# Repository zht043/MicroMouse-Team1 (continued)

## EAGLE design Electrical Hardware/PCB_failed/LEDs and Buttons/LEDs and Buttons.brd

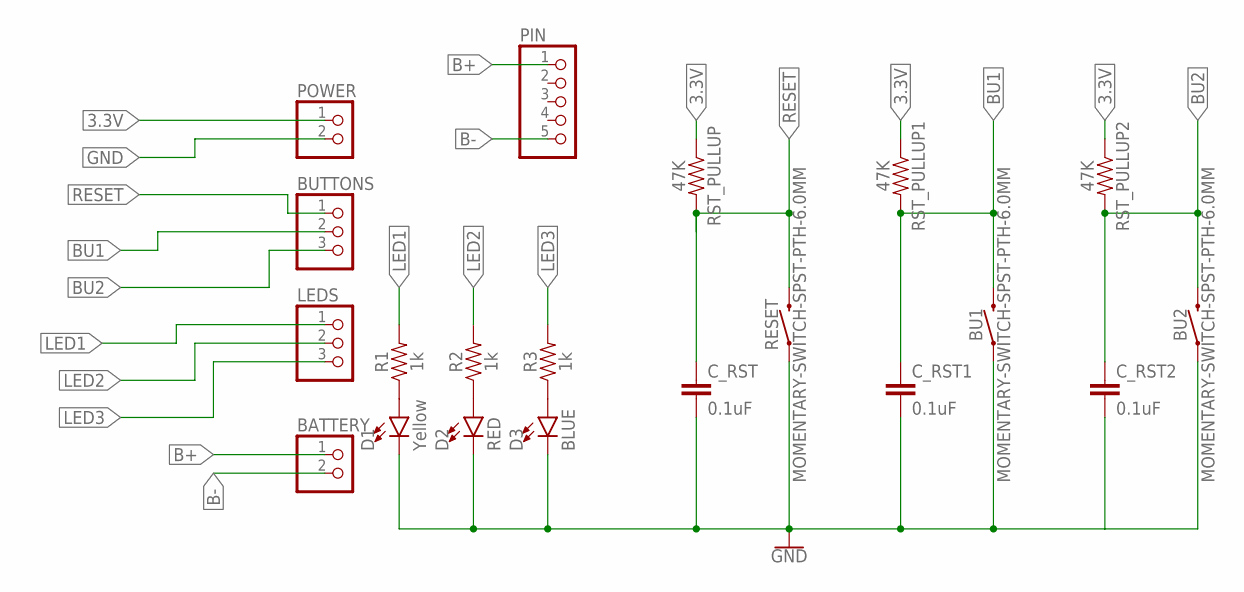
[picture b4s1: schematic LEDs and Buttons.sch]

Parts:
BATTERY: PINHD-1X2; 1X02
BU1, BU2: MOMENTARY-SWITCH-SPST-PTH-6.0MM; TACTILE_SWITCH_PTH_6.0MM
BUTTONS: PINHD-1X3; 1X03
C_RST, C_RST1, C_RST2: 0.1uF; 0805
D1: Yellow; LED-1206
D2: RED; LED-1206
D3: BLUE; LED-1206
LEDS: PINHD-1X3; 1X03
PIN: PINHD-1X55X2MM; 1_05X2MM
POWER: PINHD-1X2; 1X02
R1, R2, R3: 1k; 0805
RESET: MOMENTARY-SWITCH-SPST-PTH-6.0MM; TACTILE_SWITCH_PTH_6.0MM
RST_PULLUP, RST_PULLUP1, RST_PULLUP2: 47K; 0805

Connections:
3.3V: POWER.1, RST_PULLUP.1, RST_PULLUP1.1, RST_PULLUP2.1
B+: BATTERY.1, PIN.1
B-: BATTERY.2, PIN.5
BU1: BU1.3 (2), BUTTONS.2, C_RST1.1, RST_PULLUP1.2
BU2: BU2.3 (2), BUTTONS.3, C_RST2.1, RST_PULLUP2.2
GND: BU1.1, BU2.1, C_RST.2, C_RST1.2, C_RST2.2, D1.C, D2.C, D3.C, POWER.2, RESET.1
LED1: LEDS.1, R1.2
LED2: LEDS.2, R2.2
LED3: LEDS.3, R3.2
unnamed: D1.A, R1.1
unnamed: D2.A, R2.1
unnamed: D3.A, R3.1
RESET: BUTTONS.1, C_RST.1, RESET.3 (2), RST_PULLUP.2

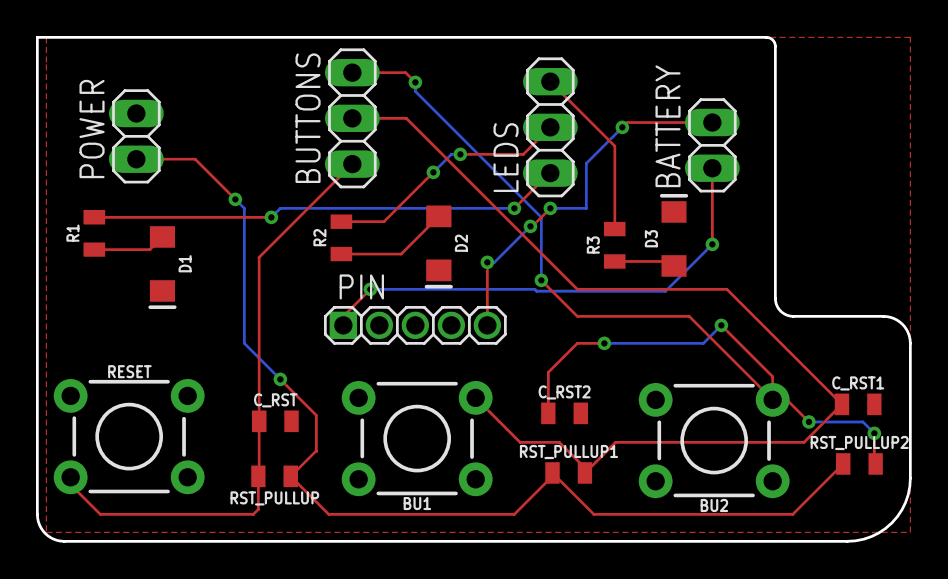
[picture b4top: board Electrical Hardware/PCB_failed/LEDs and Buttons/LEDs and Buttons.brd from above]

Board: 2 copper layers, 48.5 x 28.0 mm, 20 parts (0 on the bottom side), 13 nets.

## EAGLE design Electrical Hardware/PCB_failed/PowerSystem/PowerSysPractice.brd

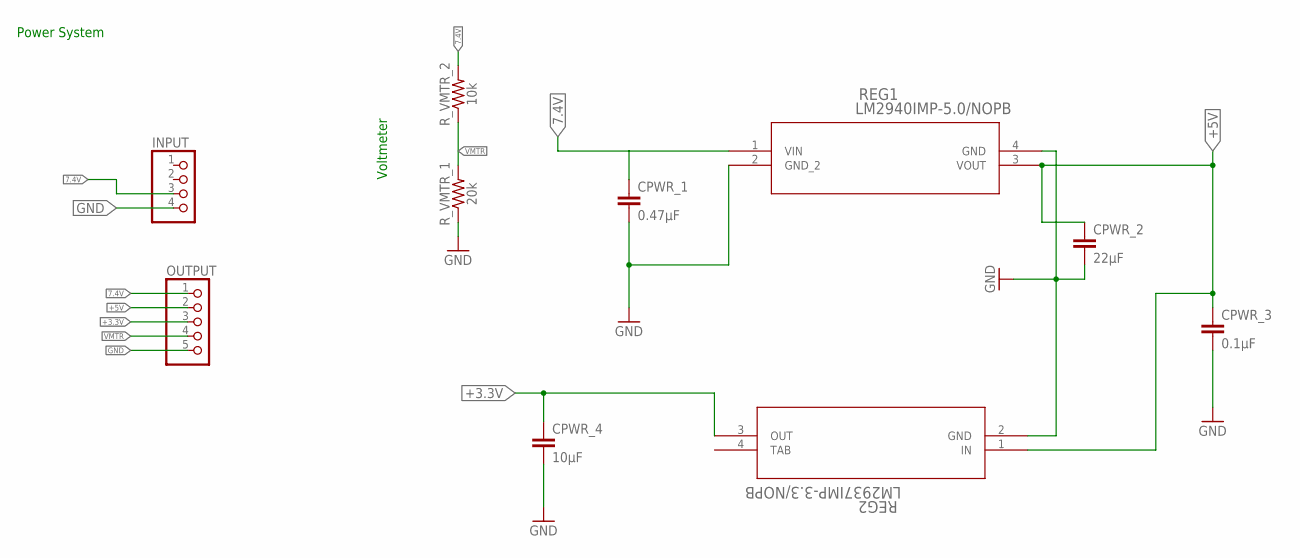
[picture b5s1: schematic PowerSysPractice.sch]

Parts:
CPWR_1: 0.47µF; 0805
CPWR_2: 22µF; 0805
CPWR_3: 0.1µF; 0805
CPWR_4: 10µF; 0805
INPUT: PINHD-1X4; 1X04
OUTPUT: PINHD-1X5; 1X05
REG1: LM2940IMP-5.0/NOPB; MP04A
REG2: LM2937IMP-3.3/NOPB; MP04A
R_VMTR_1: 20k; 0805
R_VMTR_2: 10k; 0805

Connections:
7.4V: CPWR_1.1, INPUT.3, OUTPUT.1, REG1.1 (VIN), R_VMTR_2.2
+3.3V: CPWR_4.1, OUTPUT.3, REG2.3 (OUT)
+5V: CPWR_2.1, CPWR_3.1, OUTPUT.2, REG1.3 (VOUT), REG2.1 (IN)
GND: CPWR_1.2, CPWR_2.2, CPWR_3.2, CPWR_4.2, INPUT.4, OUTPUT.5, REG1.2 (GND_2), REG1.4 (GND), REG2.2 (GND), R_VMTR_1.1
TAB: REG2.4 (TAB)
VMTR: OUTPUT.4, R_VMTR_1.2, R_VMTR_2.1

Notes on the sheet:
Power System
Voltmeter

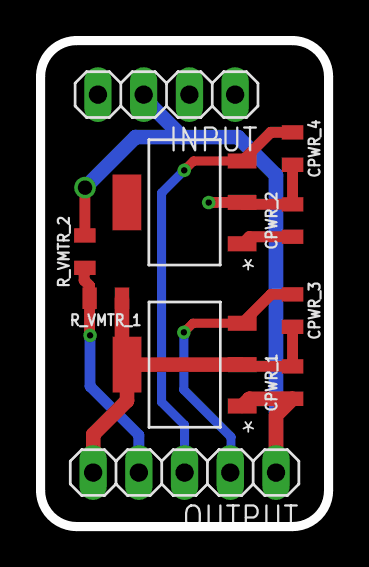
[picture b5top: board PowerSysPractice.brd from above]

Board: 2 copper layers, 16.0 x 27.0 mm, 10 parts (0 on the bottom side), 5 nets.

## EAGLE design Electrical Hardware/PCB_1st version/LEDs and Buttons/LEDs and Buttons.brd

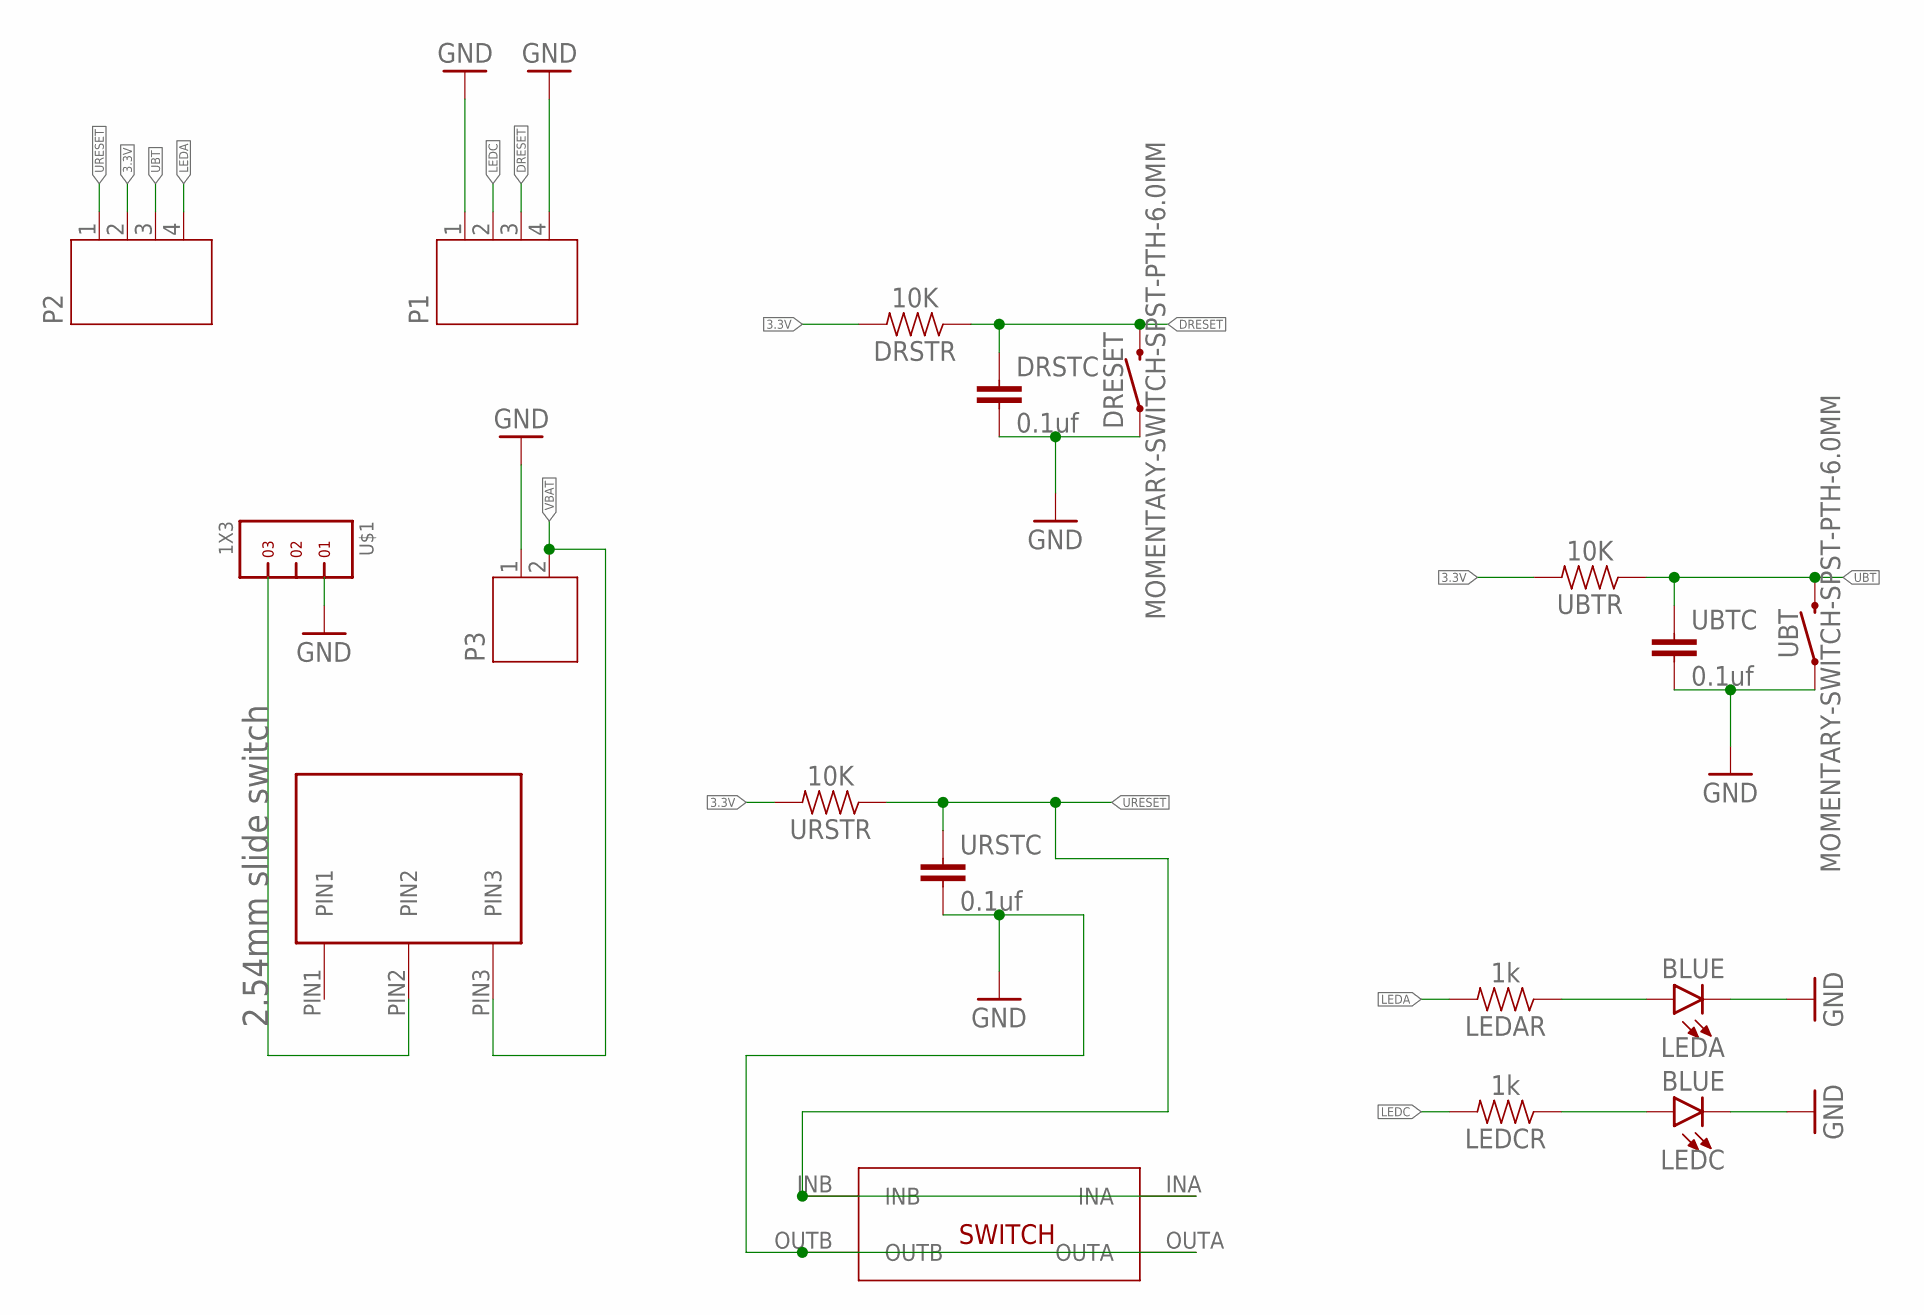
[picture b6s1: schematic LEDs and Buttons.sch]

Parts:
DRESET: MOMENTARY-SWITCH-SPST-PTH-6.0MM; TACTILE_SWITCH_PTH_6.0MM
DRSTC: 0.1uf; 0805
DRSTR: 10K; 0805
LEDA: BLUE; LED-1206
LEDAR: 1k; 0805
LEDC: BLUE; LED-1206
LEDCR: 1k; 0805
P1, P2: JST-PH4
P3: JST-PH2
U$1: 1X3
U$2: 4X4X1.5_SMD_SWITCH
U$14: TS02_SWITCH
UBT: MOMENTARY-SWITCH-SPST-PTH-6.0MM; TACTILE_SWITCH_PTH_6.0MM
UBTC: 0.1uf; 0805
UBTR: 10K; 0805
URSTC: 0.1uf; 0805
URSTR: 10K; 0805

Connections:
3.3V: DRSTR.2, P2.2, UBTR.2, URSTR.2
DRESET: DRESET.3 (2), DRSTC.1, DRSTR.1, P1.3
GND: DRESET.1, DRSTC.2, LEDA.C, LEDC.C, P1.1, P1.4, P3.1, U$1.1, U$2.OUTA, U$2.OUTB, UBT.1, UBTC.2, URSTC.2
LEDA: LEDAR.2, P2.4
LEDC: LEDCR.2, P1.2
unnamed: LEDC.A, LEDCR.1
unnamed: U$1.3, U$14.PIN2
unnamed: LEDA.A, LEDAR.1
UBT: P2.3, UBT.3 (2), UBTC.1, UBTR.1
URESET: P2.1, U$2.INA, U$2.INB, URSTC.1, URSTR.1
VBAT: P3.2, U$14.PIN3

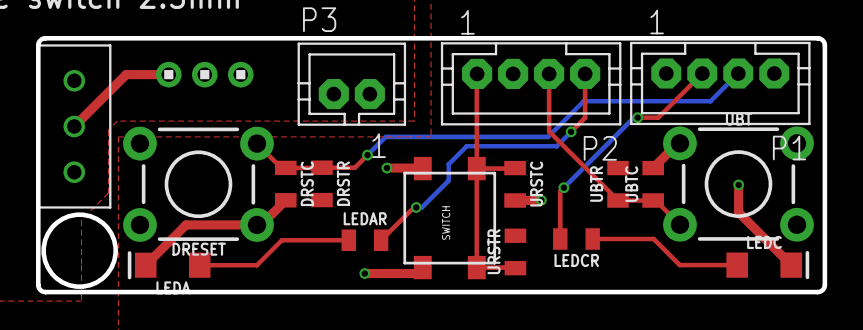
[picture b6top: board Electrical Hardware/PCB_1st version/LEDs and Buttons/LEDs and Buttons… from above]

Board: 2 copper layers, 43.7 x 14.1 mm, 18 parts (0 on the bottom side), 11 nets.

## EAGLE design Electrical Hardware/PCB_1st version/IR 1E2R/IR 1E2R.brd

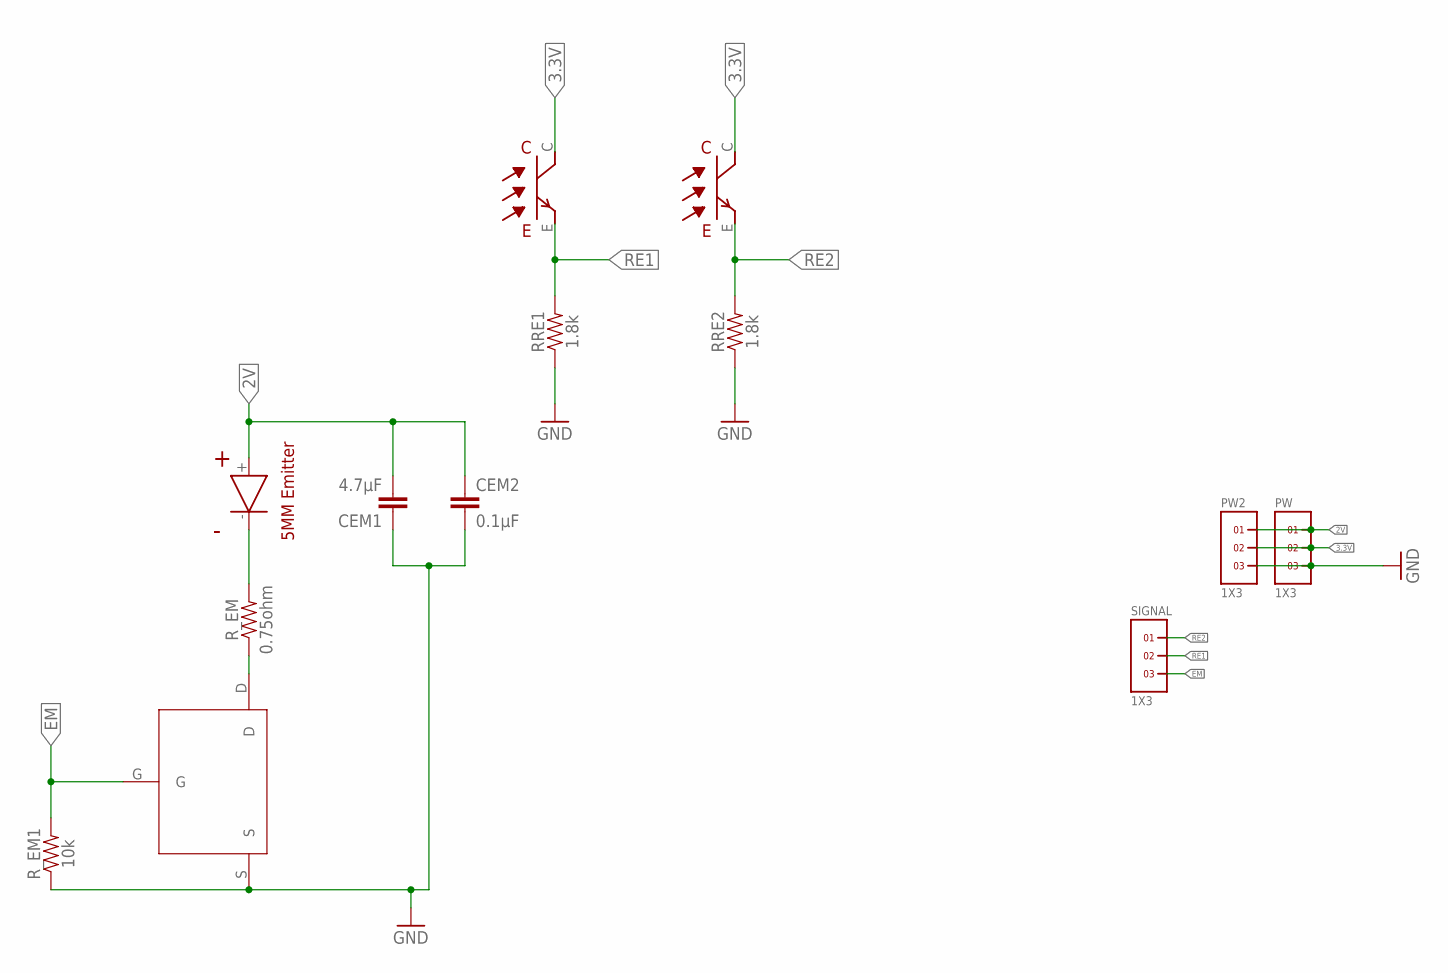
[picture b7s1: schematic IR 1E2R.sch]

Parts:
CEM1: 4.7µF; 0805
CEM2: 0.1µF; 0805
PW, PW2: 1X3
RECEIVER1, RECEIVER2: RECEIVER
RRE1, RRE2: 1.8k; 0805
R_EM: 0.75ohm; 0805
R_EM1: 10k; 0805
SIGNAL: 1X3
U$1: MCH3474
U$21: EMITTER

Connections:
2V: CEM1.2, CEM2.1, PW.1, PW2.1, U$21.+
3.3V: PW.2, PW2.2, RECEIVER1.C, RECEIVER2.C
EM: R_EM1.2, SIGNAL.3, U$1.G
EM-: R_EM.2, U$21.-
GND: CEM1.1, CEM2.2, PW.3, PW2.3, RRE1.1, RRE2.1, R_EM1.1, U$1.S
unnamed: R_EM.1, U$1.D
RE1: RECEIVER1.E, RRE1.2, SIGNAL.2
RE2: RECEIVER2.E, RRE2.2, SIGNAL.1

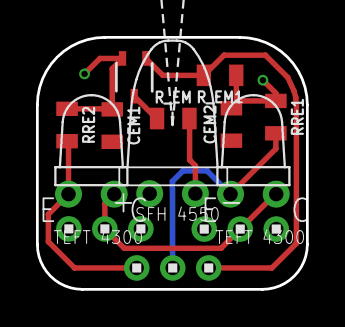
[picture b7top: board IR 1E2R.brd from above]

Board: 2 copper layers, 15.0 x 14.0 mm, 13 parts (0 on the bottom side), 8 nets.

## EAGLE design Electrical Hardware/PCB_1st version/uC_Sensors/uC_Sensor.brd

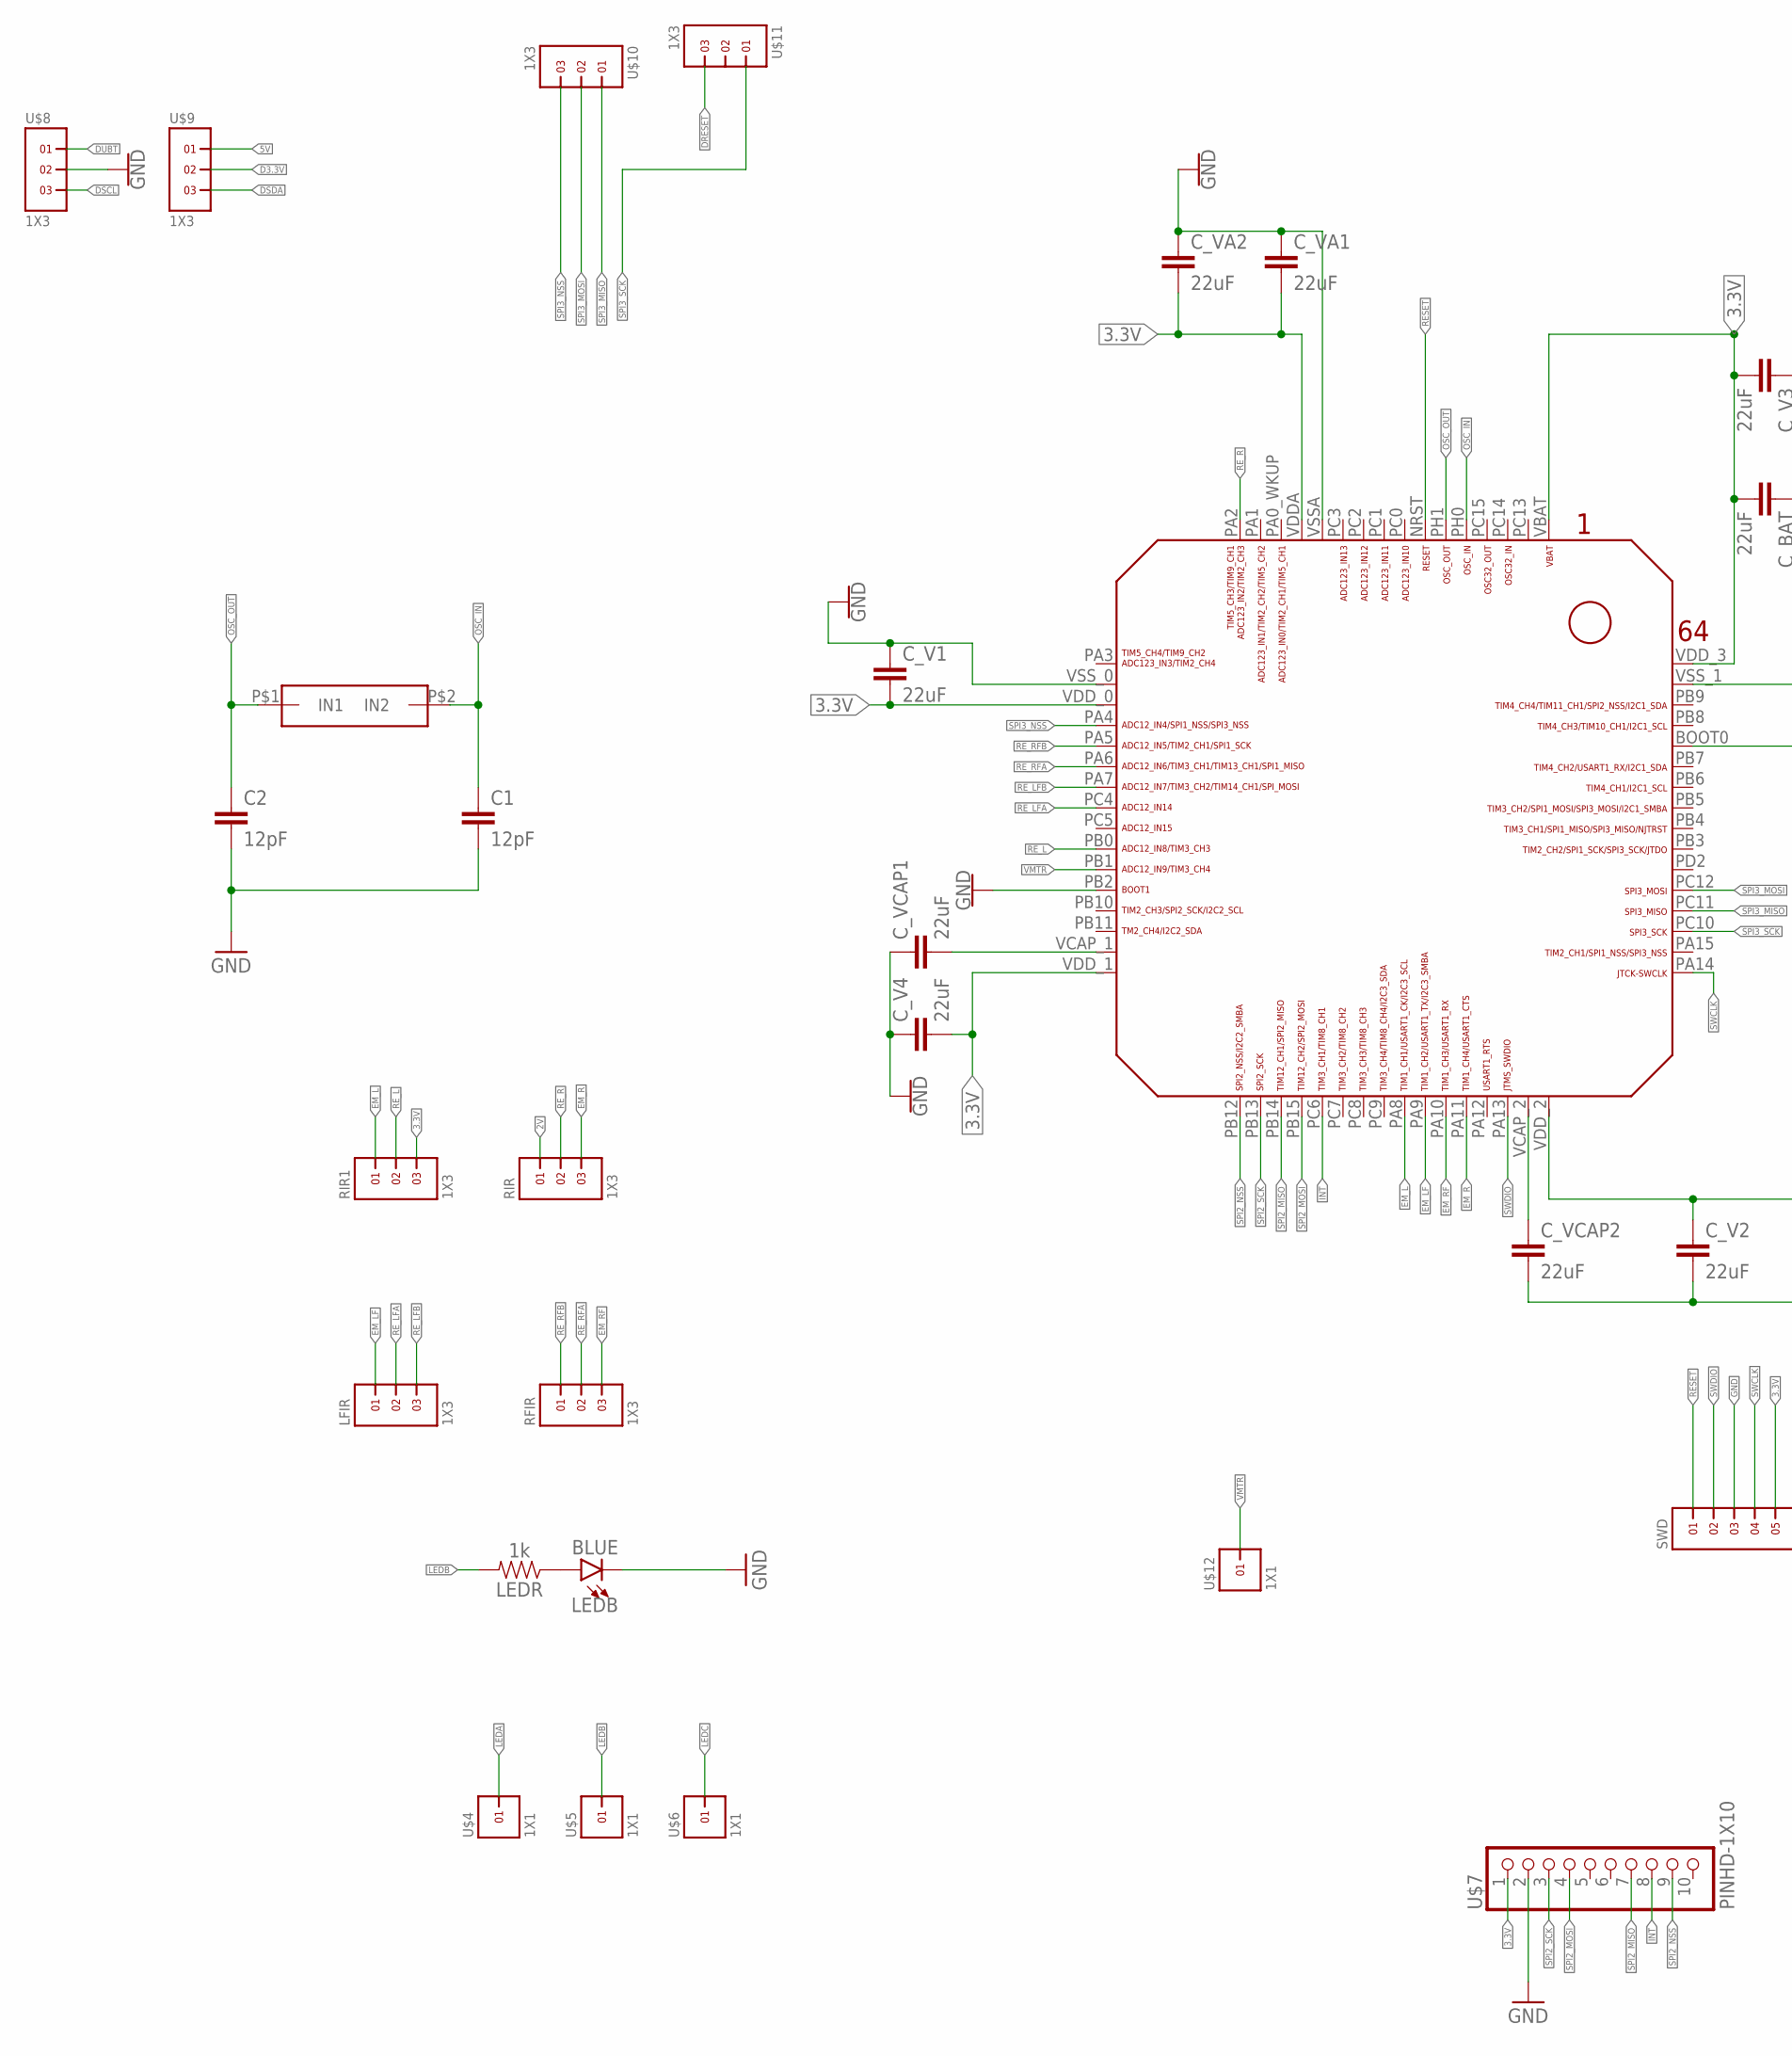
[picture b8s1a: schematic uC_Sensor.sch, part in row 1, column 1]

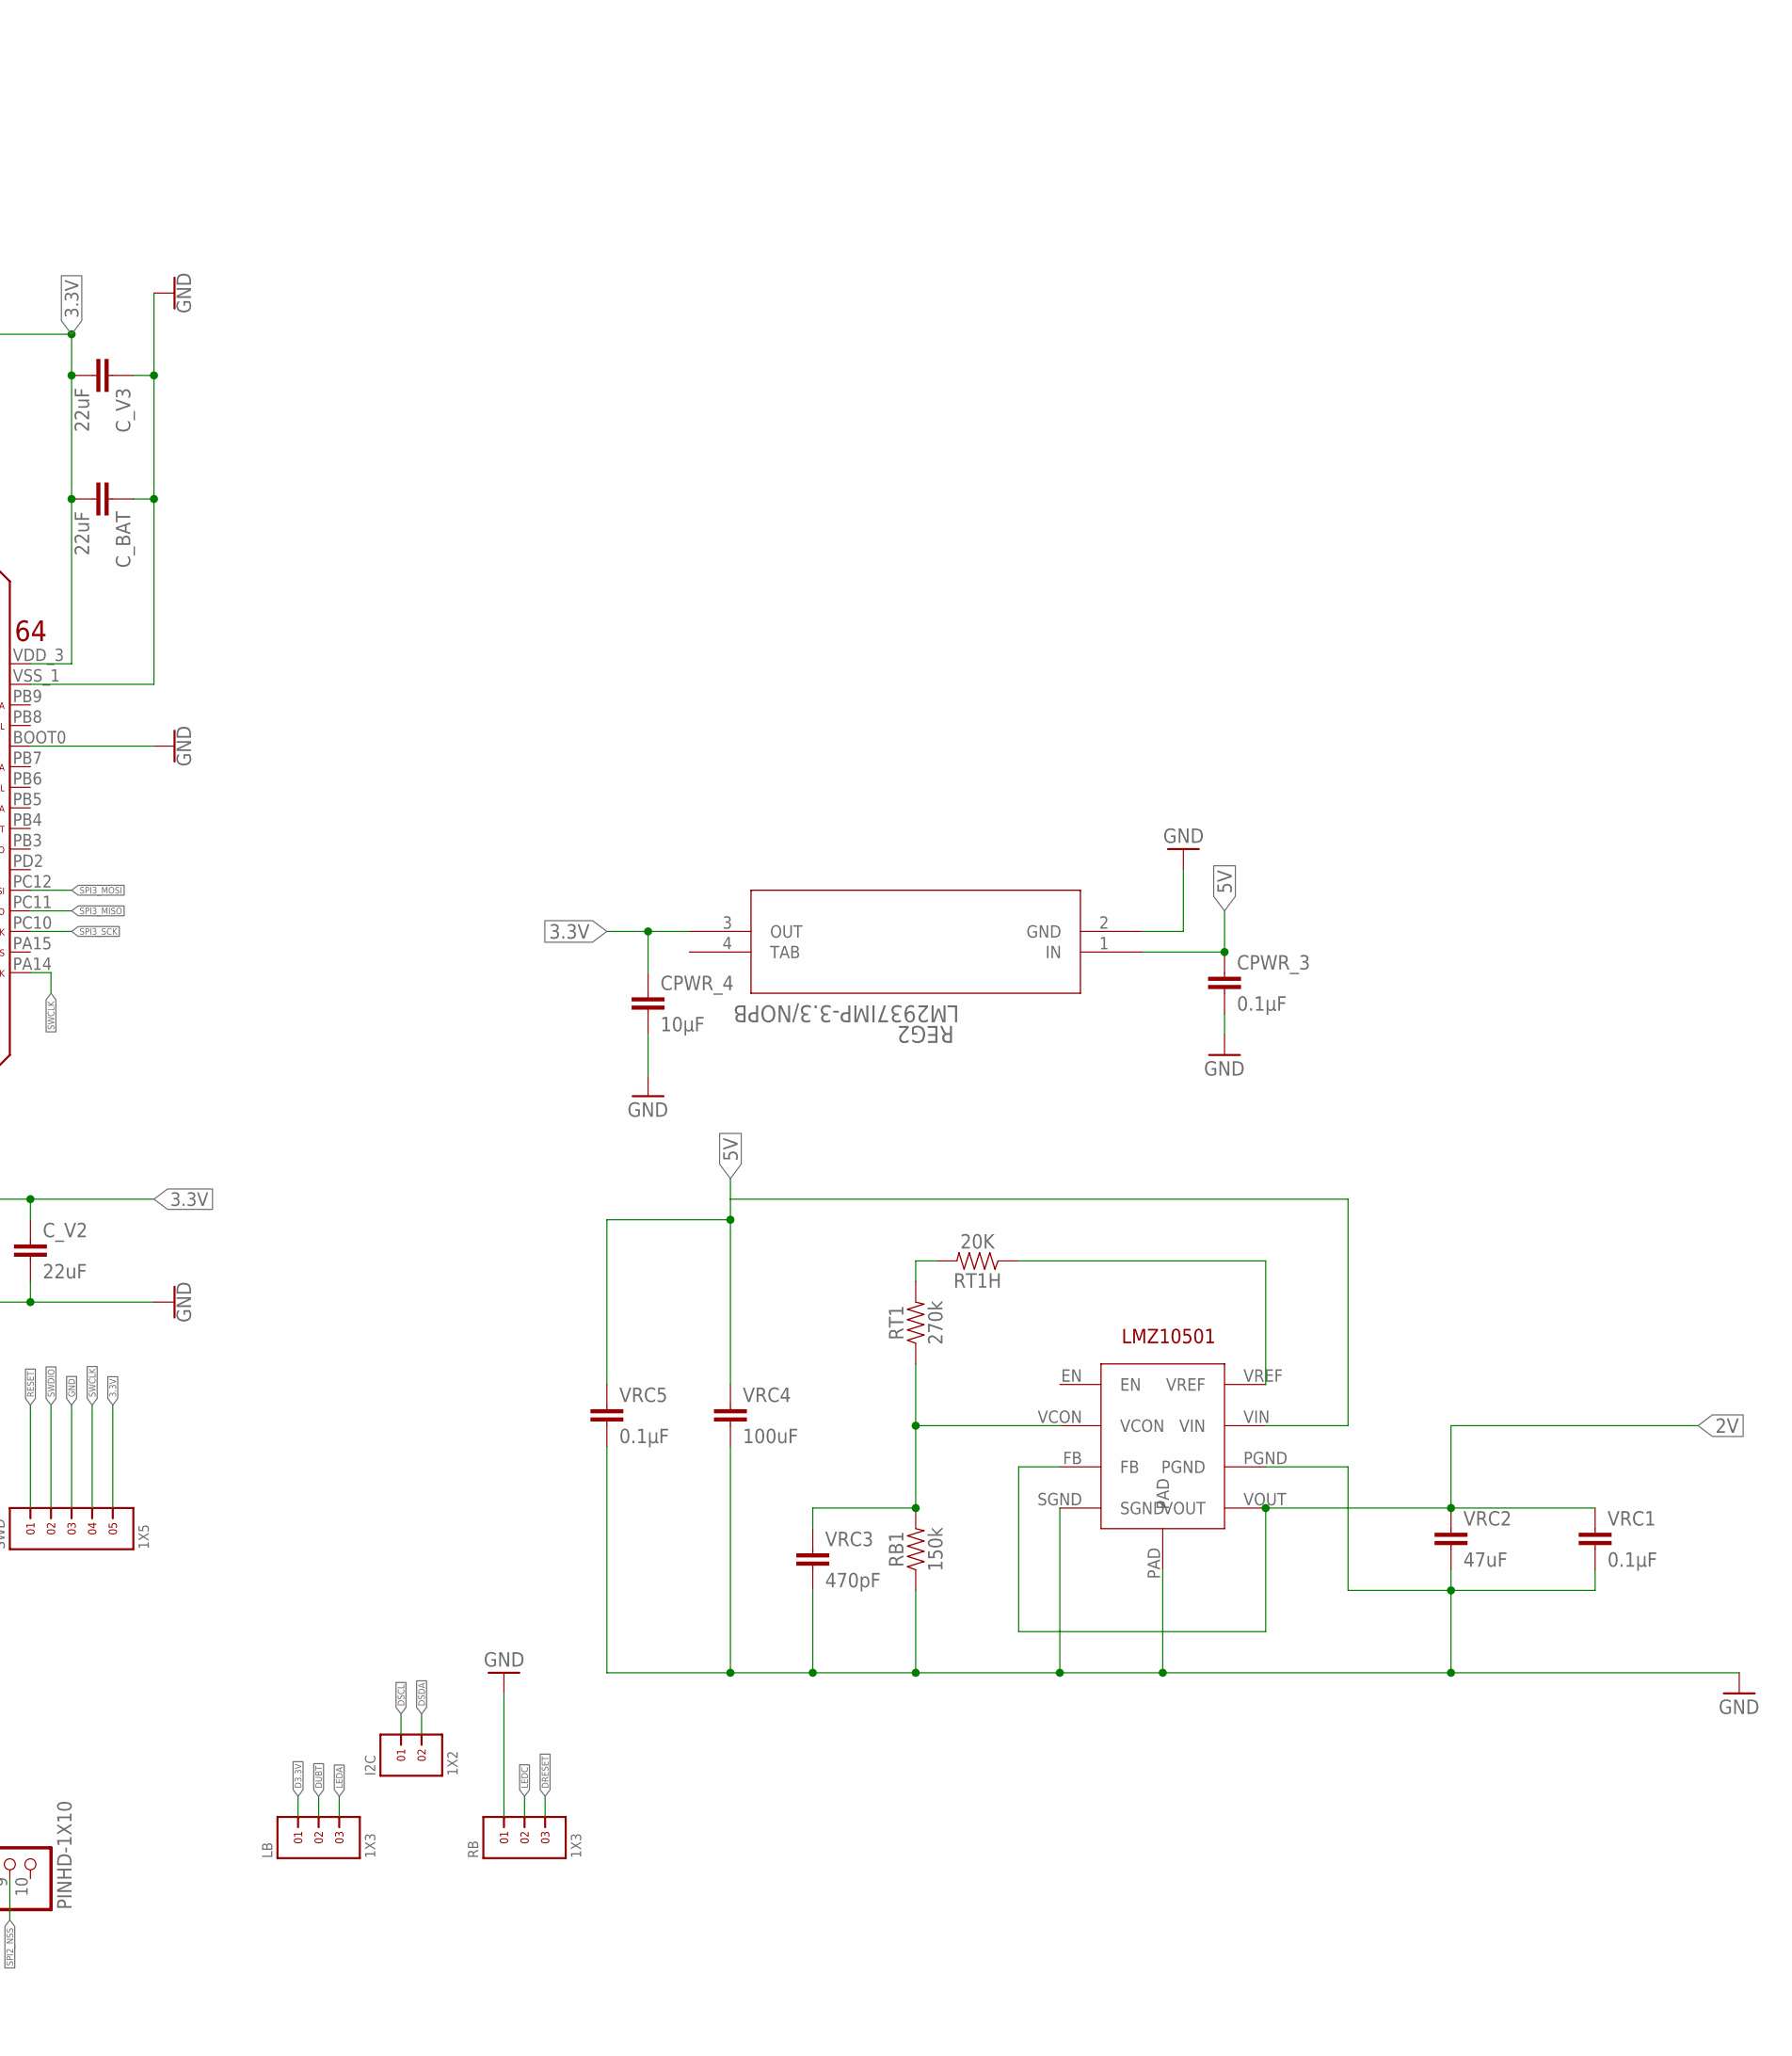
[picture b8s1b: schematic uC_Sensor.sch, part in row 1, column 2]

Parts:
C1, C2: 12pF; 0603
CPWR_3: 0.1µF; 0805@2
CPWR_4: 10µF; 0805@2
C_BAT: 22uF; 0805
C_V1, C_V2, C_V3, C_V4: 22uF; 0805
C_VA1, C_VA2: 22uF; 0805
C_VCAP1, C_VCAP2: 22uF; 0805
I2C: 1X2
LB: 1X3
LEDB: BLUE; LED-1206
LEDR: 1k; 0805
LFIR: 1X3
RB: 1X3
RB1: 150k; 0805
REG2: LM2937IMP-3.3/NOPB; MP04A
RFIR: 1X3
RIR, RIR1: 1X3
RT1: 270k; 0805
RT1H: 20K; 0805
SWD: 1X5
U$1: STM32F405/415_LQFP64
U$2: OSC
U$3: LMZ10501
U$4, U$5, U$6, U$12: 1X1
U$7: PINHD-1X10; 1X10-BIG
U$8, U$9, U$10, U$11: 1X3
VRC1, VRC5: 0.1µF; 0805@2
VRC2: 47uF; 0805@2
VRC3: 470pF; 0805@2
VRC4: 100uF; 0805@2

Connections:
2V: RIR.1, U$3.FB, U$3.VOUT, VRC1.1, VRC2.1
3.3V: CPWR_4.1, C_BAT.2, C_V1.2, C_V2.1, C_V3.2, C_V4.2, C_VA1.2, C_VA2.2, REG2.3 (OUT), RIR1.3, SWD.5, U$1.VBAT, U$1.VDDA, U$1.VDD_0, U$1.VDD_1, U$1.VDD_2, U$1.VDD_3, U$7.1
5V: CPWR_3.1, REG2.1 (IN), U$3.VIN, U$9.1, VRC4.1, VRC5.1
D3.3V: LB.1, U$9.2
DRESET: RB.3, U$11.3
DSCL: I2C.1, U$8.3
DSDA: I2C.2, U$9.3
DUBT: LB.2, U$8.1
EM_L: RIR1.1, U$1.PA8
EM_LF: LFIR.1, U$1.PA9
EM_R: RIR.3, U$1.PA11
EM_RF: RFIR.3, U$1.PA10
GND: C1.2, C2.2, CPWR_3.2, CPWR_4.2, C_BAT.1, C_V1.1, C_V2.2, C_V3.1, C_V4.1, C_VA1.1, C_VA2.1, C_VCAP1.1, C_VCAP2.2, LEDB.C, RB.1, RB1.1, REG2.2 (GND), SWD.3, U$1.BOOT0, U$1.PB2, U$1.VSSA, U$1.VSS_0, U$1.VSS_1, U$3.PAD, U$3.PGND, U$3.SGND, U$7.2, U$8.2, VRC1.2, VRC2.2, VRC3.2, VRC4.2, VRC5.2
INT: U$1.PC6, U$7.8
LEDA: LB.3, U$4.1
LEDB: LEDR.2, U$5.1
LEDC: RB.2, U$6.1
unnamed: RT1.2, RT1H.2
unnamed: RB1.2, RT1.1, U$3.VCON, VRC3.1
unnamed: RT1H.1, U$3.VREF
unnamed: LEDB.A, LEDR.1
OSC_IN: C1.1, U$1.PH0, U$2.P$2 (IN2)
OSC_OUT: C2.1, U$1.PH1, U$2.P$1 (IN1)
RESET: SWD.1, U$1.NRST
RE_L: RIR1.2, U$1.PB0
RE_LFA: LFIR.2, U$1.PC4
RE_LFB: LFIR.3, U$1.PA7
RE_R: RIR.2, U$1.PA2
RE_RFA: RFIR.2, U$1.PA6
RE_RFB: RFIR.1, U$1.PA5
SPI2_MISO: U$1.PB14, U$7.7
SPI2_MOSI: U$1.PB15, U$7.4
SPI2_NSS: U$1.PB12, U$7.9
SPI2_SCK: U$1.PB13, U$7.3
SPI3_MISO: U$1.PC11, U$10.1
SPI3_MOSI: U$1.PC12, U$10.2
SPI3_NSS: U$1.PA4, U$10.3
SPI3_SCK: U$1.PC10, U$11.1
SWCLK: SWD.4, U$1.PA14
SWDIO: SWD.2, U$1.PA13
TAB: REG2.4 (TAB)
VCAP_1: C_VCAP1.2, U$1.VCAP_1
VCAP_2: C_VCAP2.1, U$1.VCAP_2
VMTR: U$1.PB1, U$12.1

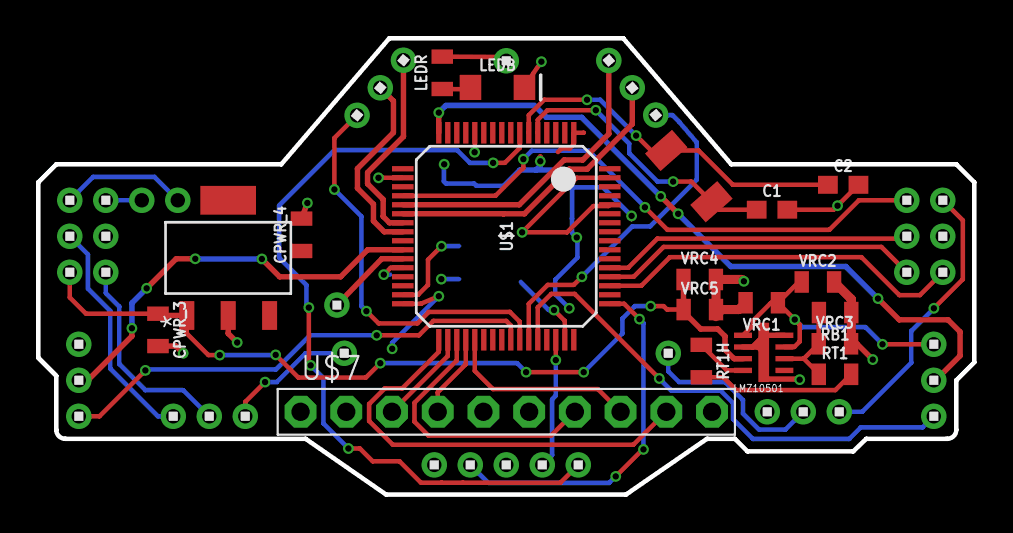
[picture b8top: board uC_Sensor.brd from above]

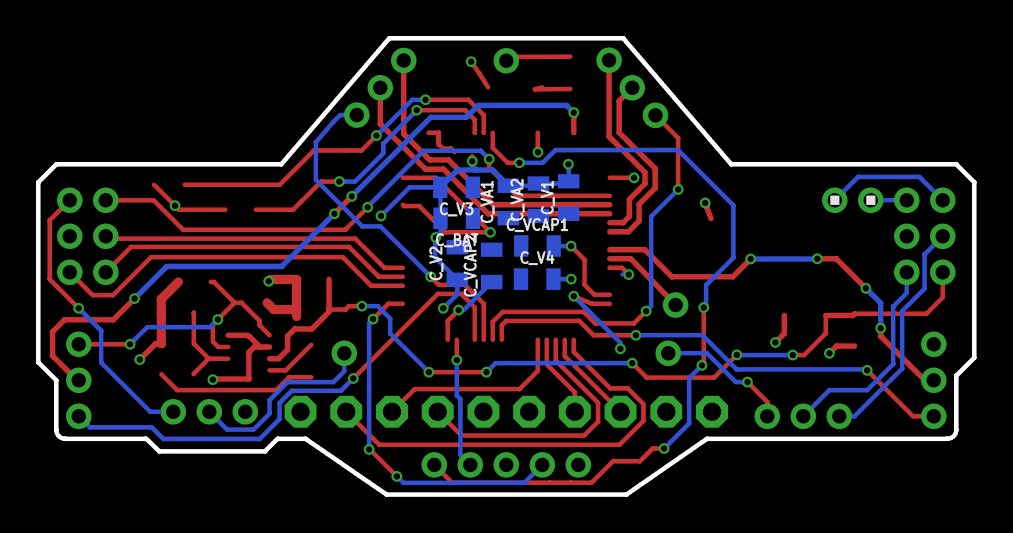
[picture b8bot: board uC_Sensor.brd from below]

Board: 2 copper layers, 52.0 x 25.4 mm, 44 parts (10 on the bottom side), 43 nets.

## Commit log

2018-03-08 arbitrary test
2018-03-08 fcucv
2018-03-08 hdyh
2018-03-08 hcjh
2018-03-08 uytdu
2018-03-10 ubiuacsb
2018-03-11 fixed some error on previous update
2018-03-11 nothing changed
2018-03-11 added mechanical hardware folder
2018-03-12 Added pic for pin reference
2018-03-12 Nothing
2018-03-12 ST reference materials
2018-03-13 Delete STD Lib Template
    Save storage space, STD template folder took too much space, we could always download this template on ST's official website
2018-03-13 add a reference pdf
2018-03-13 Deleted unneccessary folders
2018-03-13 Added unfinished SPI.c SPI.h
2018-03-25 xxxx
2018-03-26 Updated SPI
2018-03-27 Replaced Template///Fixed Errors
    The older version's template was damaged, it won't work on device such as "f40xx 41xxx
2018-03-27 fix error
2018-03-29 Updated USART.c USART.h
2018-03-29 added bunch pdfs
2018-03-30 ufifiu
2018-03-31 Added STD Example
2018-04-01 add mouser receipt
2018-04-06 Lots of changes
2018-04-08 general update
2018-04-15 Config 405 chip
2018-04-22 3week Meeting
2018-04-22 overwrite myself
2018-04-23 partial c code
2018-04-28 update USART
2018-04-29 000000
2018-04-29 PCB 3rd version
2018-04-29 PCB 3rd v upd
2018-05-01 Finshing PCB 3rd version Peripheral Board
2018-05-03 motor tester
2018-05-03 xxxooo
2018-05-05 update PCB 3rd v
2018-05-05 updated ADC
2018-05-05 Update SPI
2018-05-06 finalized PCB
2018-05-06 minor updates
2018-05-07 update Interrupt
2018-05-07 Fixed ADC problems
2018-05-12 Timer Interrupt
2018-05-12 temp
2018-05-12 floodfill
2018-05-14 Overwrite
2018-05-14 resolve merge conflict
2018-05-14 resolve merge conflicts
2018-05-14 rename mm folder
2018-05-15 IR readings
2018-05-15 Revert "IR readings"
    This reverts commit 7ffad07f1cbb3d3cd54bcbddc103bf1a12a12f0d.
2018-05-15 Revert "Revert "IR readings""
    This reverts commit c804b46515297fe7e4da5a3f733dcb047e72166f.
2018-05-17 to COS
2018-05-20 update gyro files
2018-05-20 test gyro
2018-05-22 IR on Mouse
2018-05-23 PID tuning
2018-05-23 Add safety guideline
2018-05-23 Organized Code
2018-05-24 PID draft
2018-05-25 PID worked
2018-05-26 WORK
2018-05-26 simulate PID
2018-05-26 PID_simulation
2018-05-26 update floodfill
2018-05-26 Updated floodfill to get it working
2018-05-27 xxxxxxx
2019-04-08 xxxxx
2023-09-12 update docs
